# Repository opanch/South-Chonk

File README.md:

# South Chonk
Full-sized Southpaw keyboard PCB commissioned by [/u/Drunknikov](https://www.reddit.com/user/drunknikov)

---

### Features

 - [full-sized southpaw layout](http://www.keyboard-layout-editor.com/#/gists/8d8c74d5d65b746d535dbf3a418dee56)  
 - powered by an [Elite-C](https://keeb.io/products/elite-c-usb-c-pro-micro-replacement-arduino-compatible-atmega32u4) controller  
 - uses [hotswap sockets](https://kbdfans.cn/products/mechanical-keyboard-switches-kailh-pcb-socket)

### Disclaimer

If you wish to run a groupbuy of this PCB, please send me an e-mail at mfmayol@up.edu.ph

###Keyboard Firmware 

- Added firmware file to compile for your needs 
- Added ASCII art to make it easy to read

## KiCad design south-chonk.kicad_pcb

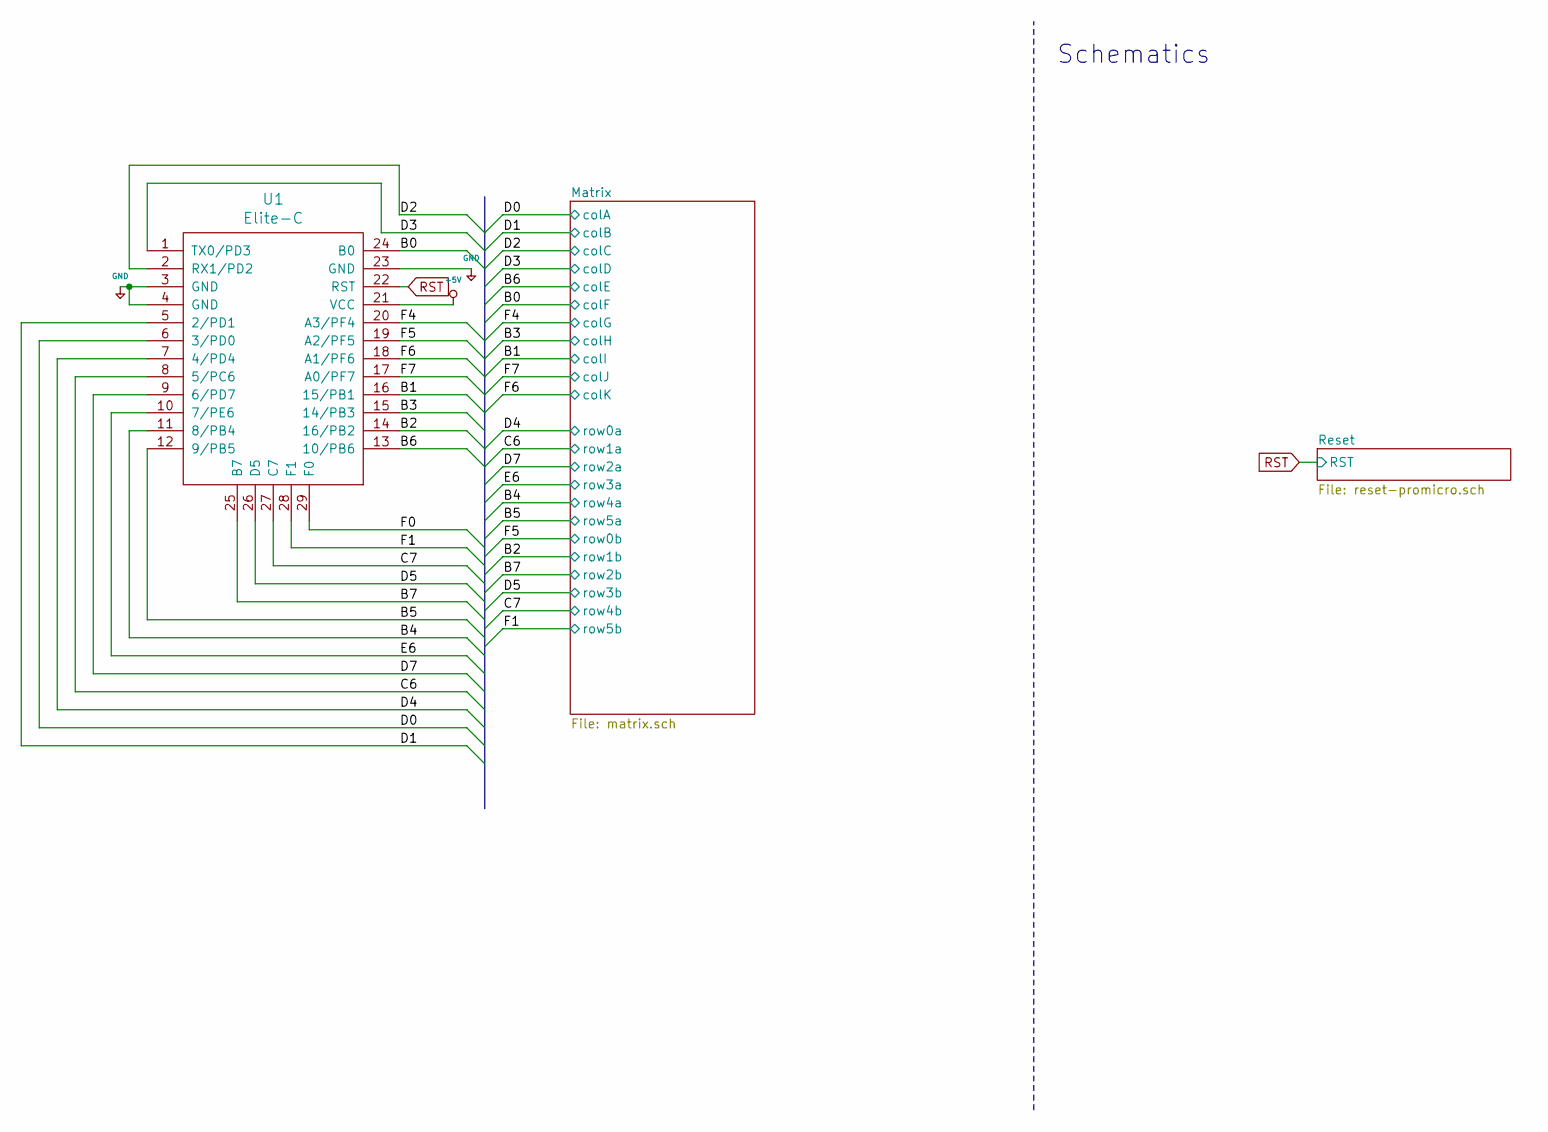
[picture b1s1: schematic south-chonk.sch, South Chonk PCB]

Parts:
U1: Elite-C

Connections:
+5V: U1.21 (VCC)
/B0: U1.24 (B0); also elsewhere on the board
/B1: U1.16 (15/PB1); also elsewhere on the board
/B2: U1.14 (16/PB2); also elsewhere on the board
/B3: U1.15 (14/PB3); also elsewhere on the board
/B4: U1.11 (8/PB4); also elsewhere on the board
/B5: U1.12 (9/PB5); also elsewhere on the board
/B6: U1.13 (10/PB6); also elsewhere on the board
/B7: U1.25 (B7); also elsewhere on the board
/C6: U1.8 (5/PC6); also elsewhere on the board
/C7: U1.27 (C7); also elsewhere on the board
/D0: U1.6 (3/PD0); also elsewhere on the board
/D1: U1.5 (2/PD1); also elsewhere on the board
/D2: U1.2 (RX1/PD2); also elsewhere on the board
/D3: U1.1 (TX0/PD3); also elsewhere on the board
/D4: U1.7 (4/PD4); also elsewhere on the board
/D5: U1.26 (D5); also elsewhere on the board
/D7: U1.9 (6/PD7); also elsewhere on the board
/E6: U1.10 (7/PE6); also elsewhere on the board
/F0: U1.29 (F0)
/F1: U1.28 (F1); also elsewhere on the board
/F4: U1.20 (A3/PF4); also elsewhere on the board
/F5: U1.19 (A2/PF5); also elsewhere on the board
/F6: U1.18 (A1/PF6); also elsewhere on the board
/F7: U1.17 (A0/PF7); also elsewhere on the board
GND: U1.3 (GND), U1.4 (GND), U1.23 (GND); also elsewhere on the board
RST: U1.22 (RST); also elsewhere on the board

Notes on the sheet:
Schematics

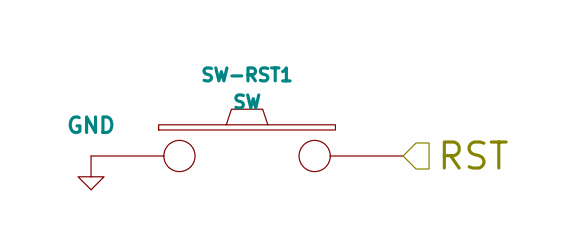
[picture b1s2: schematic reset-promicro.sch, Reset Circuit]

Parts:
SW-RST1: SW; SW_Tactile_SPST_Angled_MJTP1117

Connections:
GND: SW-RST1.1; also elsewhere on the board
RST: SW-RST1.2; also elsewhere on the board

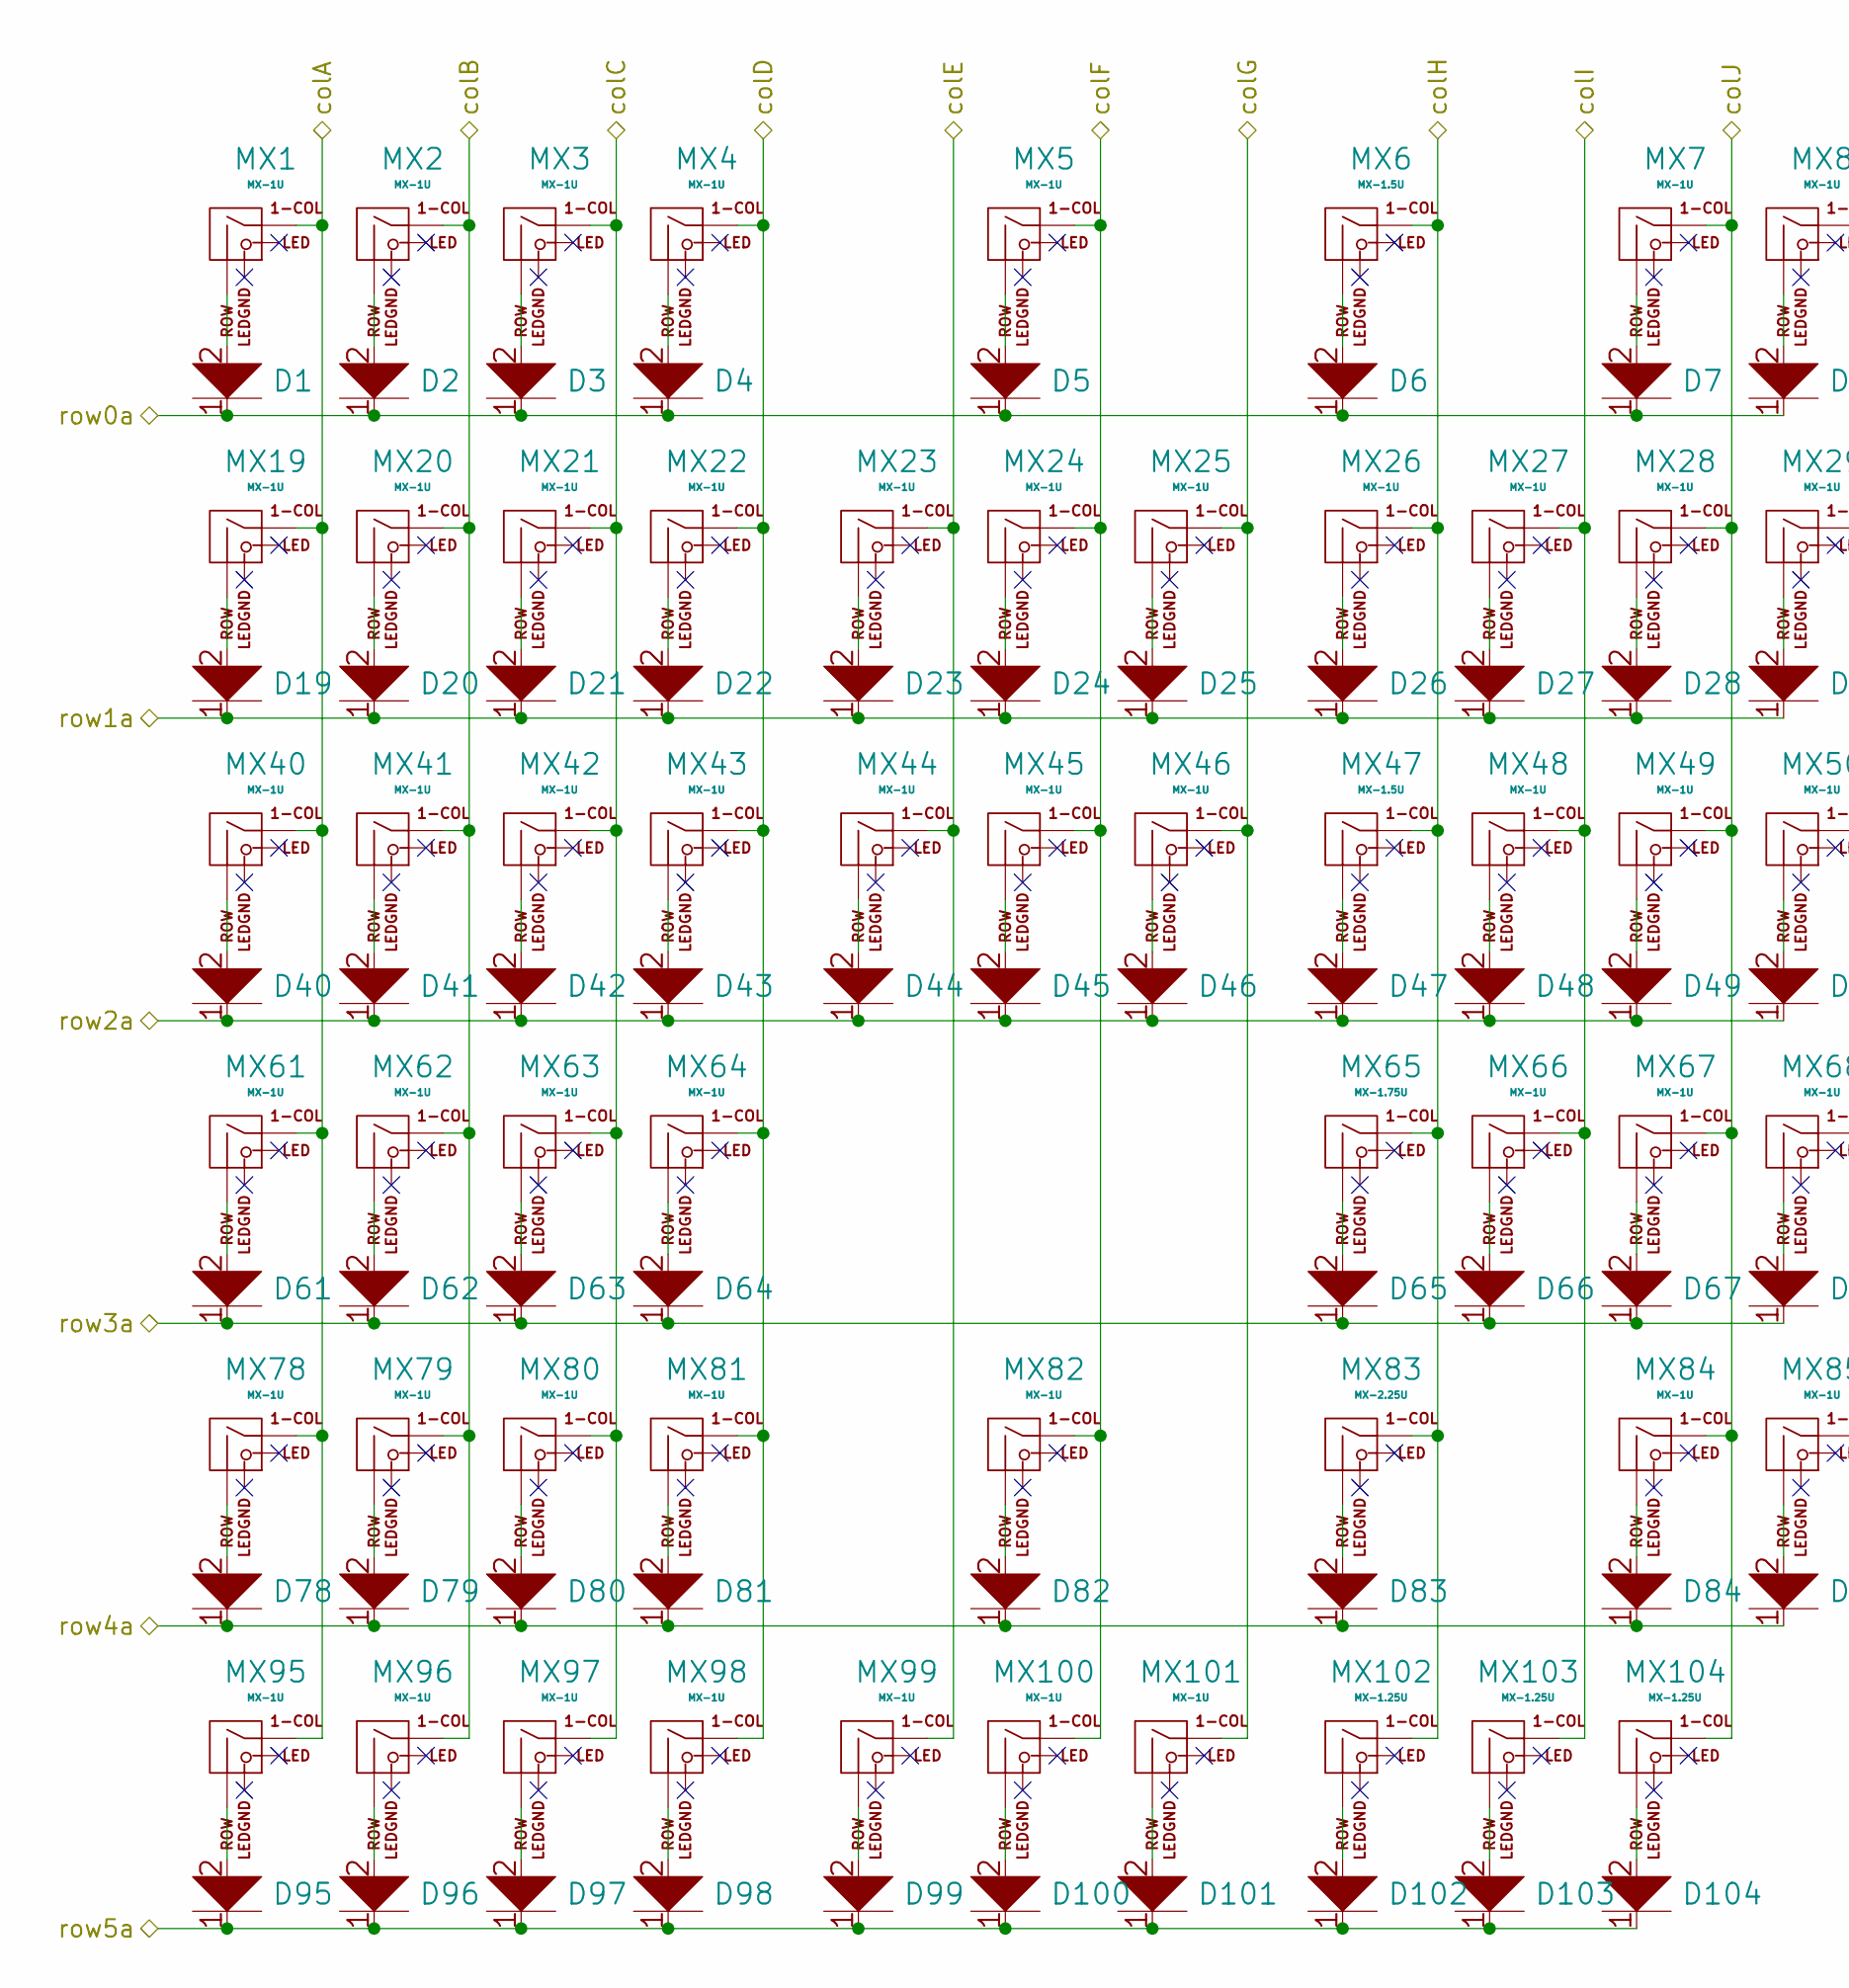
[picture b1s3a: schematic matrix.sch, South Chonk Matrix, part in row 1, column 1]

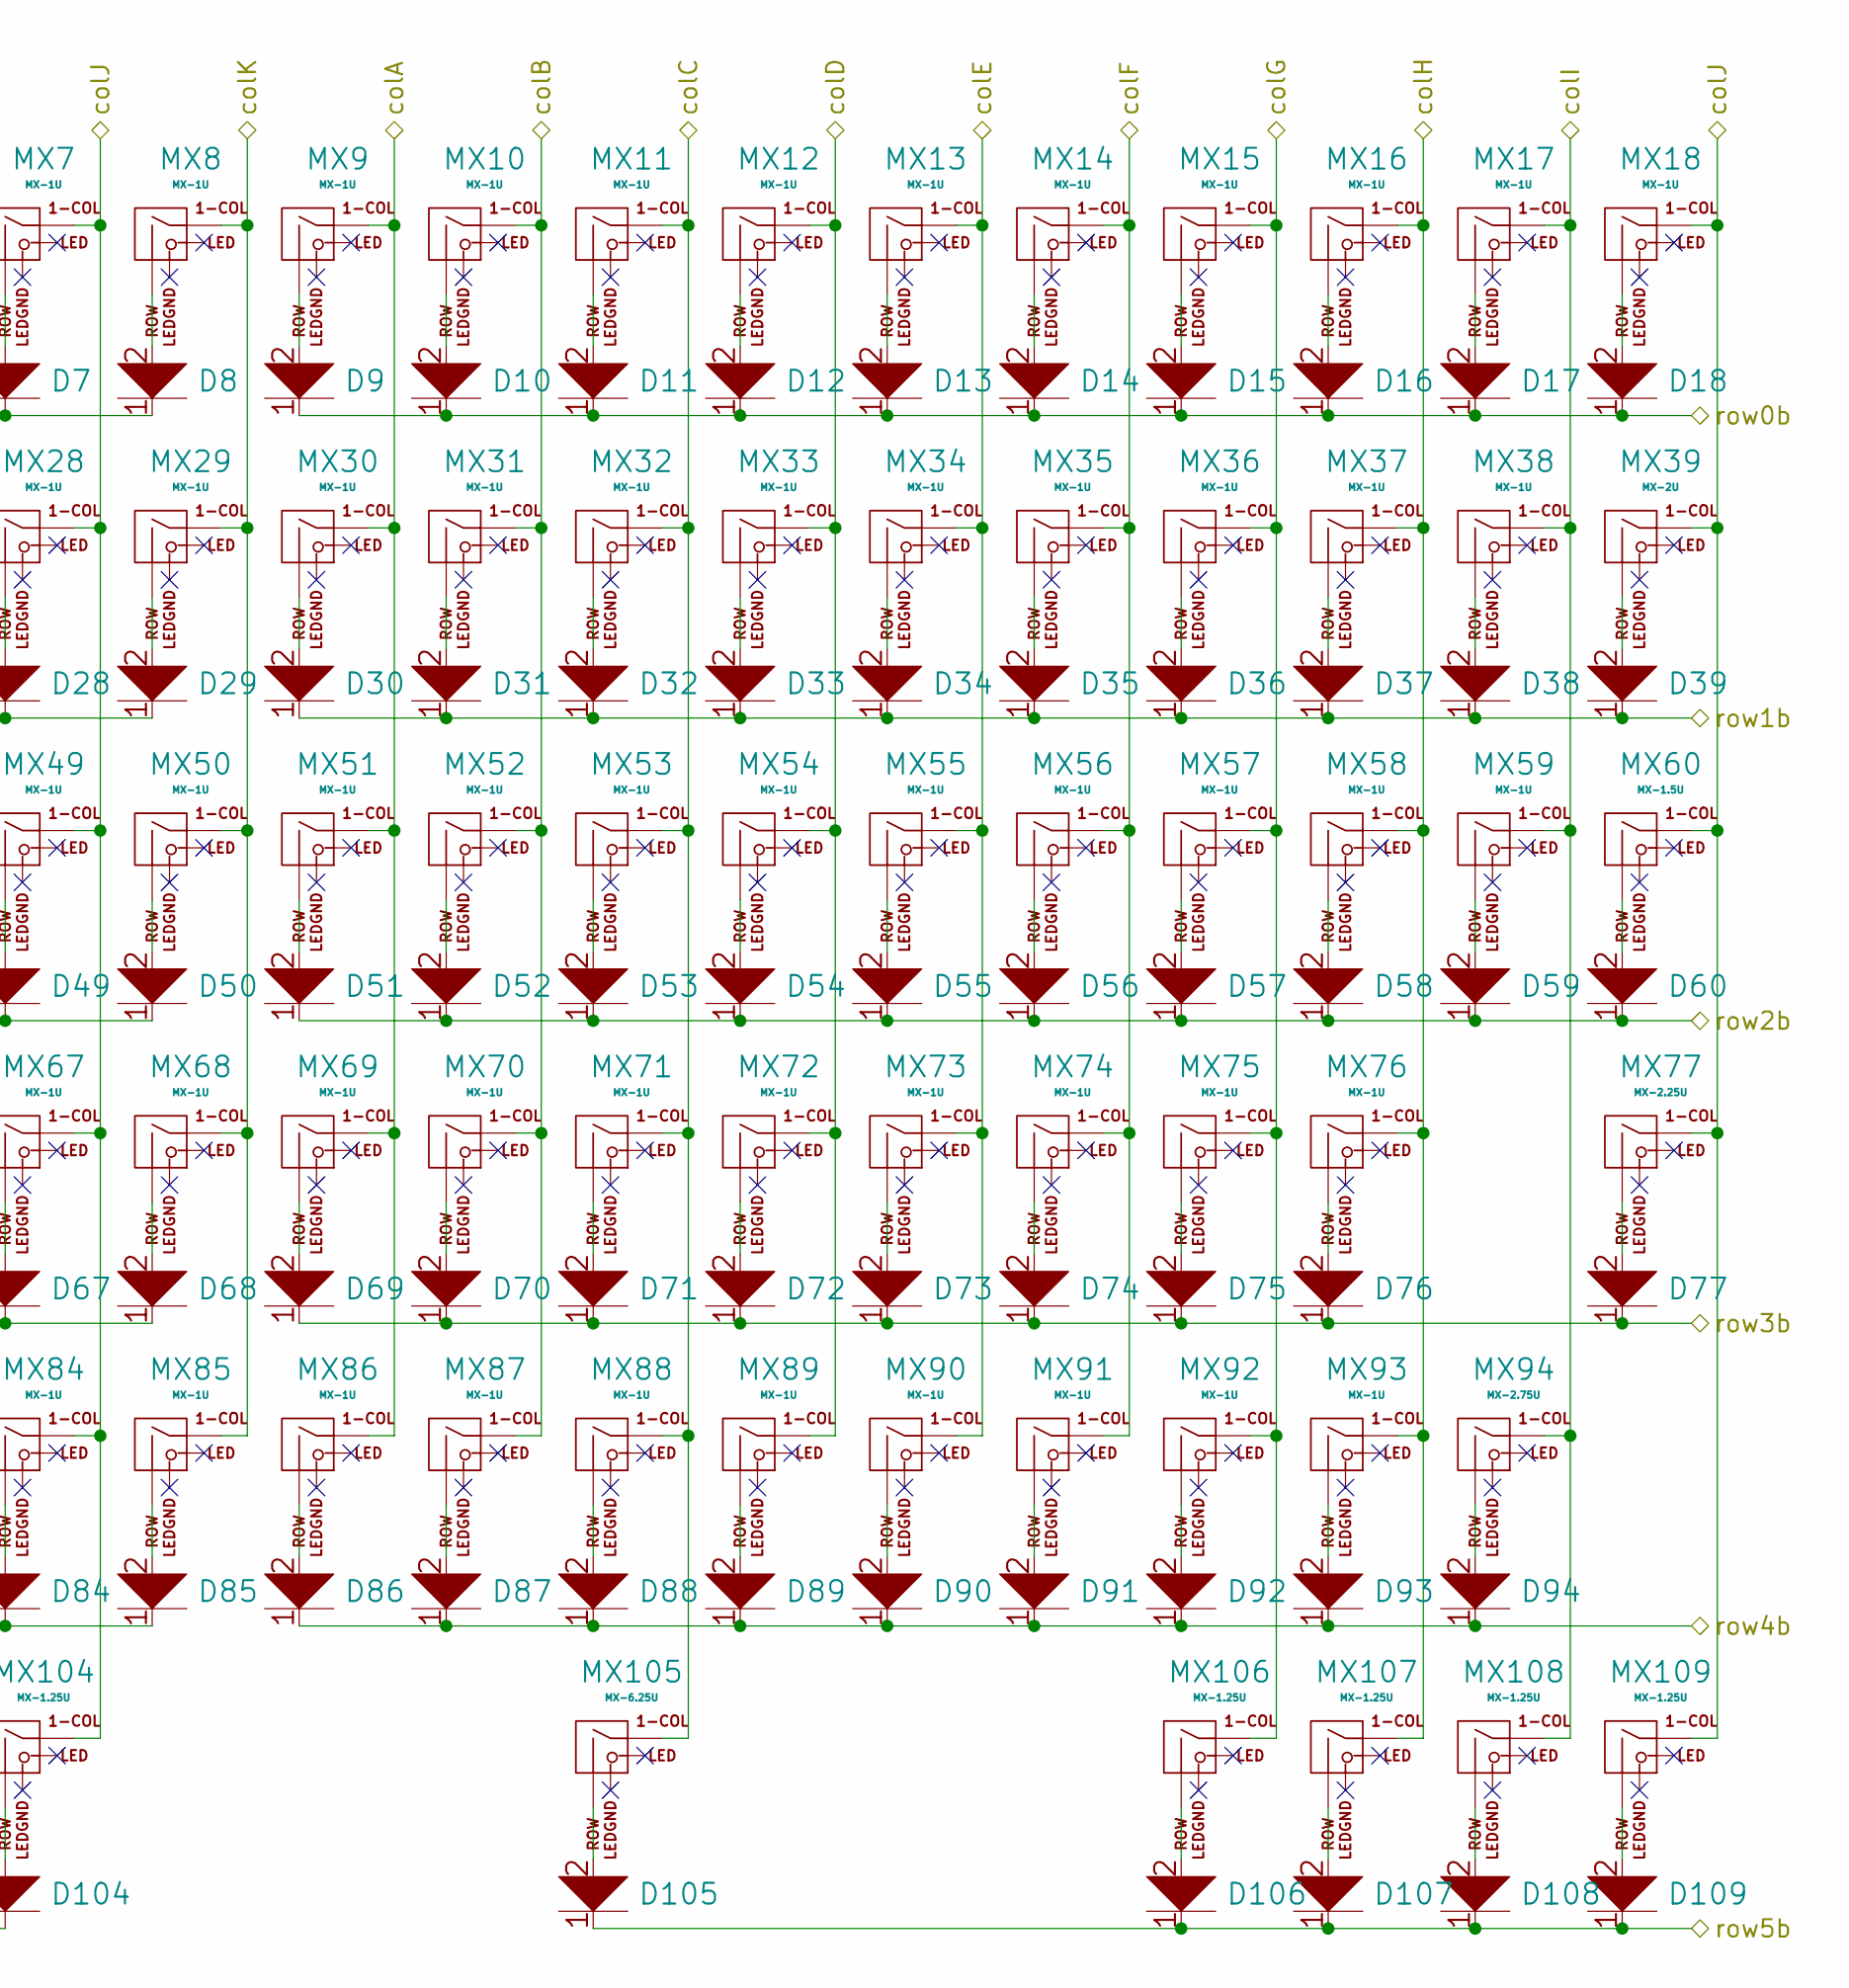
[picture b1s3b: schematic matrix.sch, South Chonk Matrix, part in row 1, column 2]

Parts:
D1, D2, D3, D4, D5, D6, D7, D8, D9, D10, D11, D12, D13, D14, D15, D16, D17, D18, D19, D20, D21, D22, D23, D24, D25, D26, D27, D28, D29, D30, D31, D32, D33, D34, D35, D36, D37, D38, D39, D40, D41, D42, D43, D44, D45, D46, D47, D48, D49, D50, D51, D52, D53, D54, D55, D56, D57, D58, D59, D60, D61, D62, D63, D64, D65, D66, D67, D68, D69, D70, D71, D72, D73, D74, D75, D76, D77, D78, D79, D80, D81, D82, D83, D84, D85, D86, D87, D88, D89, D90, D91, D92, D93, D94, D95, D96, D97, D98, D99, D100, D101, D102, D103, D104, D105, D106, D107, D108, D109: D; Diode-Hybrid-Back
MX1, MX2, MX3, MX4, MX5, MX7, MX8, MX9, MX10, MX11, MX12, MX13, MX14, MX15, MX16, MX17, MX18, MX19, MX20, MX21, MX22, MX23, MX24, MX25, MX26, MX27, MX28, MX29, MX30, MX31, MX32, MX33, MX34, MX35, MX36, MX37, MX38, MX40, MX41, MX42, MX43, MX44, MX45, MX46, MX48, MX49, MX50, MX51, MX52, MX53, MX54, MX55, MX56, MX57, MX58, MX59, MX61, MX62, MX63, MX64, MX66, MX67, MX68, MX69, MX70, MX71, MX72, MX73, MX74, MX75, MX76, MX78, MX79, MX80, MX81, MX82, MX84, MX85, MX86, MX87, MX88, MX89, MX90, MX91, MX92, MX93, MX95, MX96, MX97, MX98, MX99, MX100, MX101: MX-1U; MXOnly-1U-Hotswap
MX6, MX47, MX60: MX-1.5U; MXOnly-1.5U-Hotswap
MX39: MX-2U; MXOnly-2U-Hotswap
MX65: MX-1.75U; MXOnly-1.75U-Hotswap
MX77, MX83: MX-2.25U; MXOnly-2.25U-Hotswap
MX94: MX-2.75U; MXOnly-2.75U-Hotswap
MX102, MX103, MX104, MX106, MX107, MX108, MX109: MX-1.25U; MXOnly-1.25U-Hotswap
MX105: MX-6.25U; MXOnly-6.25U-Hotswap-ReversedStabilizers

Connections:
/B0: MX5.1 (COL), MX14.1 (COL), MX24.1 (COL), MX35.1 (COL), MX45.1 (COL), MX56.1 (COL), MX74.1 (COL), MX82.1 (COL), MX91.1 (COL), MX100.1 (COL); also elsewhere on the board
/B1: MX17.1 (COL), MX27.1 (COL), MX38.1 (COL), MX48.1 (COL), MX59.1 (COL), MX66.1 (COL), MX94.1 (COL), MX103.1 (COL), MX108.1 (COL); also elsewhere on the board
/B2: D30.1, D31.1, D32.1, D33.1, D34.1, D35.1, D36.1, D37.1, D38.1, D39.1; also elsewhere on the board
/B3: MX6.1 (COL), MX16.1 (COL), MX26.1 (COL), MX37.1 (COL), MX47.1 (COL), MX58.1 (COL), MX65.1 (COL), MX76.1 (COL), MX83.1 (COL), MX93.1 (COL), MX102.1 (COL), MX107.1 (COL); also elsewhere on the board
/B4: D78.1, D79.1, D80.1, D81.1, D82.1, D83.1, D84.1, D85.1; also elsewhere on the board
/B5: D95.1, D96.1, D97.1, D98.1, D99.1, D100.1, D101.1, D102.1, D103.1, D104.1; also elsewhere on the board
/B6: MX13.1 (COL), MX23.1 (COL), MX34.1 (COL), MX44.1 (COL), MX55.1 (COL), MX73.1 (COL), MX90.1 (COL), MX99.1 (COL); also elsewhere on the board
/B7: D51.1, D52.1, D53.1, D54.1, D55.1, D56.1, D57.1, D58.1, D59.1, D60.1; also elsewhere on the board
/C6: D19.1, D20.1, D21.1, D22.1, D23.1, D24.1, D25.1, D26.1, D27.1, D28.1, D29.1; also elsewhere on the board
/C7: D86.1, D87.1, D88.1, D89.1, D90.1, D91.1, D92.1, D93.1, D94.1; also elsewhere on the board
/D0: MX1.1 (COL), MX9.1 (COL), MX19.1 (COL), MX30.1 (COL), MX40.1 (COL), MX51.1 (COL), MX61.1 (COL), MX69.1 (COL), MX78.1 (COL), MX86.1 (COL), MX95.1 (COL); also elsewhere on the board
/D1: MX2.1 (COL), MX10.1 (COL), MX20.1 (COL), MX31.1 (COL), MX41.1 (COL), MX52.1 (COL), MX62.1 (COL), MX70.1 (COL), MX79.1 (COL), MX87.1 (COL), MX96.1 (COL); also elsewhere on the board
/D2: MX3.1 (COL), MX11.1 (COL), MX21.1 (COL), MX32.1 (COL), MX42.1 (COL), MX53.1 (COL), MX63.1 (COL), MX71.1 (COL), MX80.1 (COL), MX88.1 (COL), MX97.1 (COL), MX105.1 (COL); also elsewhere on the board
/D3: MX4.1 (COL), MX12.1 (COL), MX22.1 (COL), MX33.1 (COL), MX43.1 (COL), MX54.1 (COL), MX64.1 (COL), MX72.1 (COL), MX81.1 (COL), MX89.1 (COL), MX98.1 (COL); also elsewhere on the board
/D4: D1.1, D2.1, D3.1, D4.1, D5.1, D6.1, D7.1, D8.1; also elsewhere on the board
/D5: D69.1, D70.1, D71.1, D72.1, D73.1, D74.1, D75.1, D76.1, D77.1; also elsewhere on the board
/D7: D40.1, D41.1, D42.1, D43.1, D44.1, D45.1, D46.1, D47.1, D48.1, D49.1, D50.1; also elsewhere on the board
/E6: D61.1, D62.1, D63.1, D64.1, D65.1, D66.1, D67.1, D68.1; also elsewhere on the board
/F1: D105.1, D106.1, D107.1, D108.1, D109.1; also elsewhere on the board
/F4: MX15.1 (COL), MX25.1 (COL), MX36.1 (COL), MX46.1 (COL), MX57.1 (COL), MX75.1 (COL), MX92.1 (COL), MX101.1 (COL), MX106.1 (COL); also elsewhere on the board
/F5: D9.1, D10.1, D11.1, D12.1, D13.1, D14.1, D15.1, D16.1, D17.1, D18.1; also elsewhere on the board
/F6: MX8.1 (COL), MX29.1 (COL), MX50.1 (COL), MX68.1 (COL), MX85.1 (COL); also elsewhere on the board
/F7: MX7.1 (COL), MX18.1 (COL), MX28.1 (COL), MX39.1 (COL), MX49.1 (COL), MX60.1 (COL), MX67.1 (COL), MX77.1 (COL), MX84.1 (COL), MX104.1 (COL), MX109.1 (COL); also elsewhere on the board
unnamed: D1.2, MX1.2 (ROW)
unnamed: D2.2, MX2.2 (ROW)
unnamed: D3.2, MX3.2 (ROW)
unnamed: D4.2, MX4.2 (ROW)
unnamed: D5.2, MX5.2 (ROW)
unnamed: D6.2, MX6.2 (ROW)
unnamed: D7.2, MX7.2 (ROW)
unnamed: D8.2, MX8.2 (ROW)
unnamed: D9.2, MX9.2 (ROW)
unnamed: D10.2, MX10.2 (ROW)
unnamed: D11.2, MX11.2 (ROW)
unnamed: D12.2, MX12.2 (ROW)
unnamed: D13.2, MX13.2 (ROW)
unnamed: D14.2, MX14.2 (ROW)
unnamed: D15.2, MX15.2 (ROW)
unnamed: D16.2, MX16.2 (ROW)
unnamed: D17.2, MX17.2 (ROW)
unnamed: D18.2, MX18.2 (ROW)
unnamed: D19.2, MX19.2 (ROW)
unnamed: D20.2, MX20.2 (ROW)
unnamed: D21.2, MX21.2 (ROW)
unnamed: D22.2, MX22.2 (ROW)
unnamed: D23.2, MX23.2 (ROW)
unnamed: D24.2, MX24.2 (ROW)
unnamed: D25.2, MX25.2 (ROW)
unnamed: D26.2, MX26.2 (ROW)
unnamed: D27.2, MX27.2 (ROW)
unnamed: D28.2, MX28.2 (ROW)
unnamed: D29.2, MX29.2 (ROW)
unnamed: D30.2, MX30.2 (ROW)
unnamed: D31.2, MX31.2 (ROW)
unnamed: D32.2, MX32.2 (ROW)
unnamed: D33.2, MX33.2 (ROW)
unnamed: D34.2, MX34.2 (ROW)
unnamed: D35.2, MX35.2 (ROW)
unnamed: D36.2, MX36.2 (ROW)
unnamed: D37.2, MX37.2 (ROW)
unnamed: D38.2, MX38.2 (ROW)
unnamed: D39.2, MX39.2 (ROW)
unnamed: D40.2, MX40.2 (ROW)
unnamed: D41.2, MX41.2 (ROW)
unnamed: D42.2, MX42.2 (ROW)
unnamed: D43.2, MX43.2 (ROW)
unnamed: D44.2, MX44.2 (ROW)
unnamed: D45.2, MX45.2 (ROW)
unnamed: D46.2, MX46.2 (ROW)
unnamed: D47.2, MX47.2 (ROW)
unnamed: D48.2, MX48.2 (ROW)
unnamed: D49.2, MX49.2 (ROW)
unnamed: D50.2, MX50.2 (ROW)
unnamed: D51.2, MX51.2 (ROW)
unnamed: D52.2, MX52.2 (ROW)
unnamed: D53.2, MX53.2 (ROW)
unnamed: D54.2, MX54.2 (ROW)
unnamed: D55.2, MX55.2 (ROW)
unnamed: D56.2, MX56.2 (ROW)
unnamed: D57.2, MX57.2 (ROW)
unnamed: D58.2, MX58.2 (ROW)
unnamed: D59.2, MX59.2 (ROW)
unnamed: D60.2, MX60.2 (ROW)
unnamed: D61.2, MX61.2 (ROW)
unnamed: D62.2, MX62.2 (ROW)
unnamed: D63.2, MX63.2 (ROW)
unnamed: D64.2, MX64.2 (ROW)
unnamed: D65.2, MX65.2 (ROW)
unnamed: D66.2, MX66.2 (ROW)
unnamed: D67.2, MX67.2 (ROW)
unnamed: D68.2, MX68.2 (ROW)
unnamed: D69.2, MX69.2 (ROW)
unnamed: D70.2, MX70.2 (ROW)
unnamed: D71.2, MX71.2 (ROW)
unnamed: D72.2, MX72.2 (ROW)
unnamed: D73.2, MX73.2 (ROW)
unnamed: D74.2, MX74.2 (ROW)
unnamed: D75.2, MX75.2 (ROW)
unnamed: D76.2, MX76.2 (ROW)
unnamed: D77.2, MX77.2 (ROW)
unnamed: D78.2, MX78.2 (ROW)
unnamed: D79.2, MX79.2 (ROW)
unnamed: D80.2, MX80.2 (ROW)
unnamed: D81.2, MX81.2 (ROW)
unnamed: D82.2, MX82.2 (ROW)
unnamed: D83.2, MX83.2 (ROW)
unnamed: D84.2, MX84.2 (ROW)
unnamed: D85.2, MX85.2 (ROW)
unnamed: D86.2, MX86.2 (ROW)
unnamed: D87.2, MX87.2 (ROW)
unnamed: D88.2, MX88.2 (ROW)
unnamed: D89.2, MX89.2 (ROW)
unnamed: D90.2, MX90.2 (ROW)
unnamed: D91.2, MX91.2 (ROW)
unnamed: D92.2, MX92.2 (ROW)
unnamed: D93.2, MX93.2 (ROW)
unnamed: D94.2, MX94.2 (ROW)
unnamed: D95.2, MX95.2 (ROW)
unnamed: D96.2, MX96.2 (ROW)
unnamed: D97.2, MX97.2 (ROW)
unnamed: D98.2, MX98.2 (ROW)
unnamed: D99.2, MX99.2 (ROW)
unnamed: D100.2, MX100.2 (ROW)
unnamed: D101.2, MX101.2 (ROW)
unnamed: D102.2, MX102.2 (ROW)
unnamed: D103.2, MX103.2 (ROW)
unnamed: D104.2, MX104.2 (ROW)
unnamed: D105.2, MX105.2 (ROW)
unnamed: D106.2, MX106.2 (ROW)
unnamed: D107.2, MX107.2 (ROW)
unnamed: D108.2, MX108.2 (ROW)
unnamed: D109.2, MX109.2 (ROW)

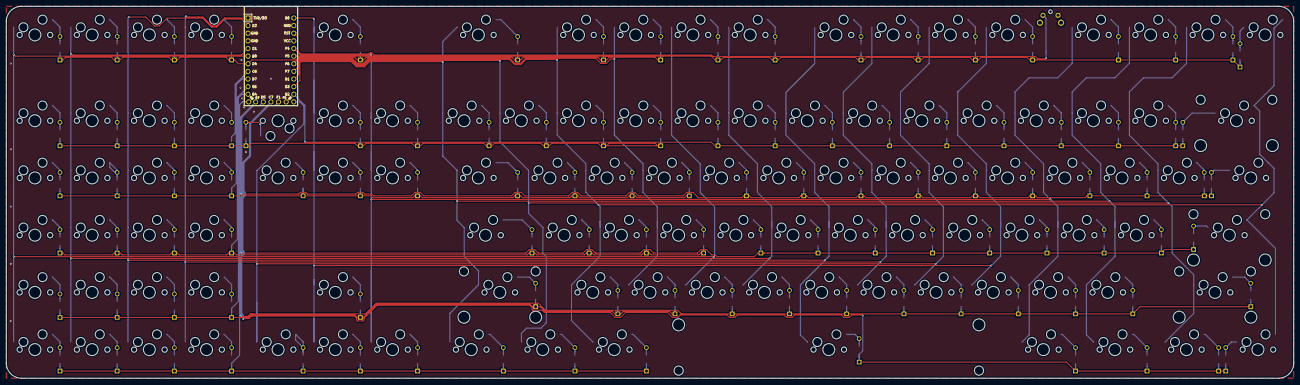
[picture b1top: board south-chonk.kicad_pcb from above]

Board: 2 copper layers, 428.6 x 123.8 mm, 220 parts (1 on the bottom side), 134 nets.

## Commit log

2019-03-26 add CC BY-SA 4.0 license
2019-03-26 Update LICENSE
2022-01-02 Add files via upload
    QMK firmware to program your keyboard

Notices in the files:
README.md:
Creative Commons Attribution-ShareAlike 4.0 International License
